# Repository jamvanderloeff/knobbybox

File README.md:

# knobbybox
some buttons n knobs for flight sim

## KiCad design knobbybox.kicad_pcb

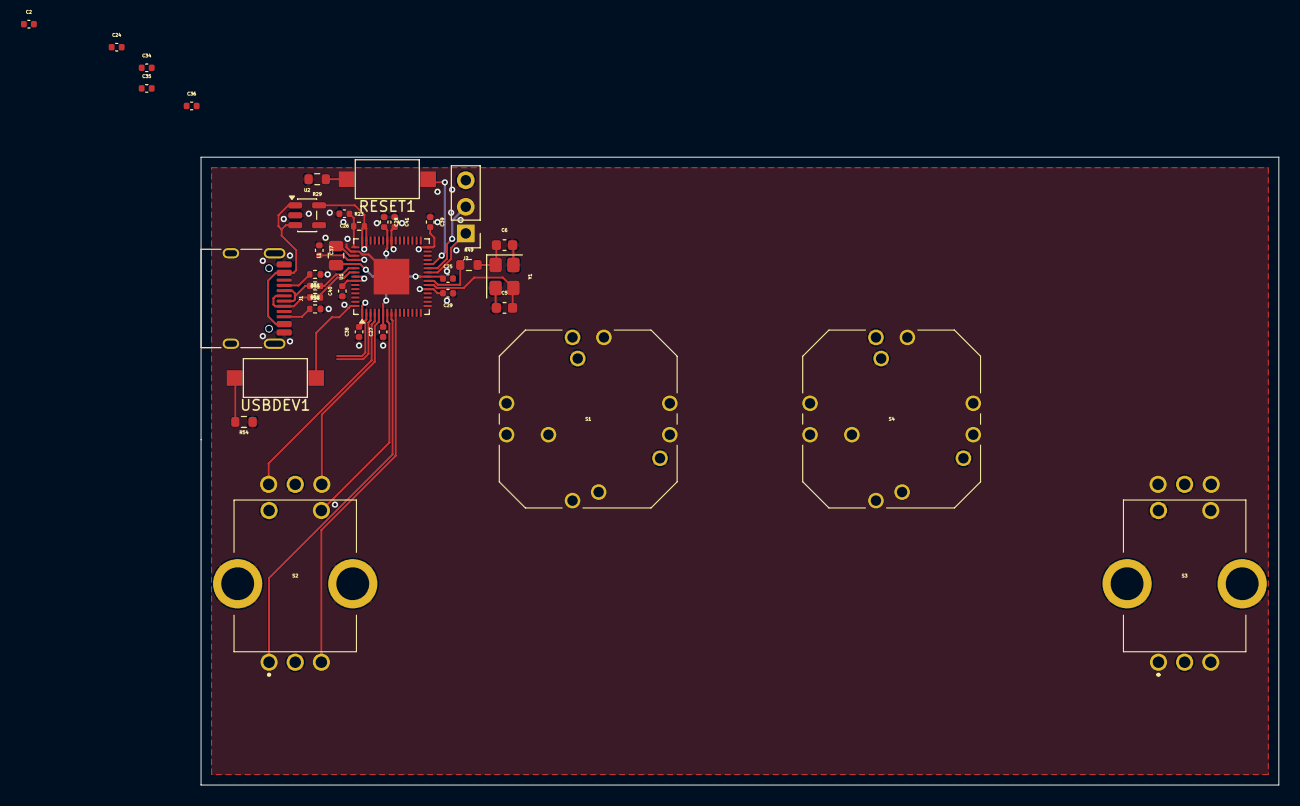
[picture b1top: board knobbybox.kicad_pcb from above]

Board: 2 copper layers, 103.0 x 60.0 mm, 37 parts (0 on the bottom side), 45 nets.

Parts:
C2, C27, C28, C29, C34, C35, C36, C37, C38, C39, C40, C41: 0.1uF; C_0402_1005Metric
C5, C6: 10pF; C_0603_1608Metric
C24, C25, C26: 4.7μF; C_0402_1005Metric
J1: USB_C_Receptacle_USB2.0_14P; USB_C_Receptacle_HRO_TYPE-C-31-M-12
J2: SWD; PinHeader_1x03_P2.54mm_Vertical
L1: L; R_0805_2012Metric
R23, R50, R51: 33Ω; R_0402_1005Metric
R29, R49, R54: 1k; R_0603_1608Metric
R52, R53: 5.1k; R_0402_1005Metric
RESET1: SW_Push; SW_SPST_CK_RS282G05A3
S1, S4: RKJXT1F42001
S2, S3: EC11EBB24C03
U1: RP2354A; QFN-60-1EP_7x7mm_P0.4mm_EP3.4x3.4mm
U2: AP2112K-3.3; SOT-23-5
USBDEV1: SW_Push; SW_SPST_CK_RS282G05A3
Y1: Crystal; Crystal_SMD_3225-4Pin_3.2x2.5mm

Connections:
+1V1: C25.1, C27.2, C28.2, L1.1, U1.6 (DVDD), U1.23 (DVDD), U1.39 (DVDD), U1.50 (VREG_FB)
+3V3: C2.2, C24.1, C29.2, C34.2, C35.2, C36.2, C37.2, C38.2, C39.2, C40.2, C41.2, R23.2, U1.1 (IOVDD), U1.11 (IOVDD), U1.20 (IOVDD), U1.30 (IOVDD), U1.38 (IOVDD), U1.44 (ADC_AVDD), U1.45 (IOVDD), U1.49 (VREG_VIN), U1.53 (USB_OTP_VDD), U1.54 (QSPI_IOVDD), U2.5 (VOUT)
/DIR_1A: S1.1 (A), U1.28 (GPIO17)
/DIR_1B: S1.4 (B), U1.31 (GPIO19)
/DIR_1C: S1.6 (C), U1.32 (GPIO20)
/DIR_1D: S1.9 (D_1), U1.27 (GPIO16)
/DIR_4A: S4.1 (A), U1.13 (GPIO9)
/DIR_4B: S4.4 (B), U1.14 (GPIO10)
/DIR_4C: S4.6 (C), U1.15 (GPIO11)
/DIR_4D: S4.9 (D_1), U1.16 (GPIO12)
/ENC_1A: S1.10 (ENCODER_A), U1.10 (GPIO7)
/ENC_1B: S1.5 (ENCODER_B), U1.12 (GPIO8)
/ENC_2A: S2.A1, U1.8 (GPIO5)
/ENC_2B: S2.A2, U1.4 (GPIO2)
/ENC_2C: S2.B1, U1.9 (GPIO6)
/ENC_2D: S2.B2, U1.5 (GPIO3)
/ENC_3A: S3.A1, U1.33 (GPIO21)
/ENC_3B: S3.A2, U1.34 (GPIO22)
/ENC_3C: S3.B1, U1.35 (GPIO23)
/ENC_3D: S3.B2, U1.36 (GPIO24)
/ENC_4A: S4.10 (ENCODER_A), U1.18 (GPIO14)
/ENC_4B: S4.5 (ENCODER_B), U1.19 (GPIO15)
/PUSH_1: S1.2 (PUSH), U1.29 (GPIO18)
/PUSH_2: S2.E1, U1.7 (GPIO4)
/PUSH_3: S3.E1, U1.37 (GPIO25)
/PUSH_4: S4.2 (PUSH), U1.17 (GPIO13)
/SIO: J2.2, U1.25 (SWDIO)
/SWC: J2.1, U1.24 (SWCLK)
/USB_DM: J1.A7 (D-), J1.B7 (D-), R50.2
/USB_DP: J1.A6 (D+), J1.B6 (D+), R51.1
/VBUS: J1.A4 (VBUS), J1.A9 (VBUS), J1.B4 (VBUS), J1.B9 (VBUS), U2.1 (VIN), U2.3 (EN)
/VREG_LX: L1.2, U1.48 (VREG_LX)
GND: C2.1, C5.1, C6.2, C24.2, C25.2, C26.2, C27.1, C28.1, C29.1, C34.1, C35.1, C36.1, C37.1, C38.1, C39.1, C40.1, C41.1, J1.A1 (GND), J1.A12 (GND), J1.B1 (GND), J1.B12 (GND), J2.3, R29.2, R52.2, R53.1, R54.2, S1.3 (GND_TERMINAL), S1.7 (COM), S1.8 (ENCODER_COM), S2.C1, S2.C2, S2.D1, S2.MH1, S2.MH2, S3.C1, S3.C2, S3.D1, S3.MH1, S3.MH2, S4.3 (GND_TERMINAL), S4.7 (COM), S4.8 (ENCODER_COM), U1.47 (VREG_PGND), U1.61 (GND), U2.2 (GND), Y1.2, Y1.4
unnamed: C6.1, R49.2, Y1.1
unnamed: J1.A5 (CC1), R53.2
unnamed: J1.B5 (CC2), R52.1
unnamed: R29.1, RESET1.2
unnamed: R54.1, USBDEV1.2
unnamed: RESET1.1, U1.26 (RUN)
unnamed: R50.1, U1.51 (USB_DM)
unnamed: R51.2, U1.52 (USB_DP)
unnamed: C26.1, R23.1, U1.46 (VREG_AVDD)
unnamed: C5.2, U1.21 (XIN), Y1.3
unnamed: R49.1, U1.22 (XOUT)
unnamed: U1.60 (~QSPI_SS), USBDEV1.1
